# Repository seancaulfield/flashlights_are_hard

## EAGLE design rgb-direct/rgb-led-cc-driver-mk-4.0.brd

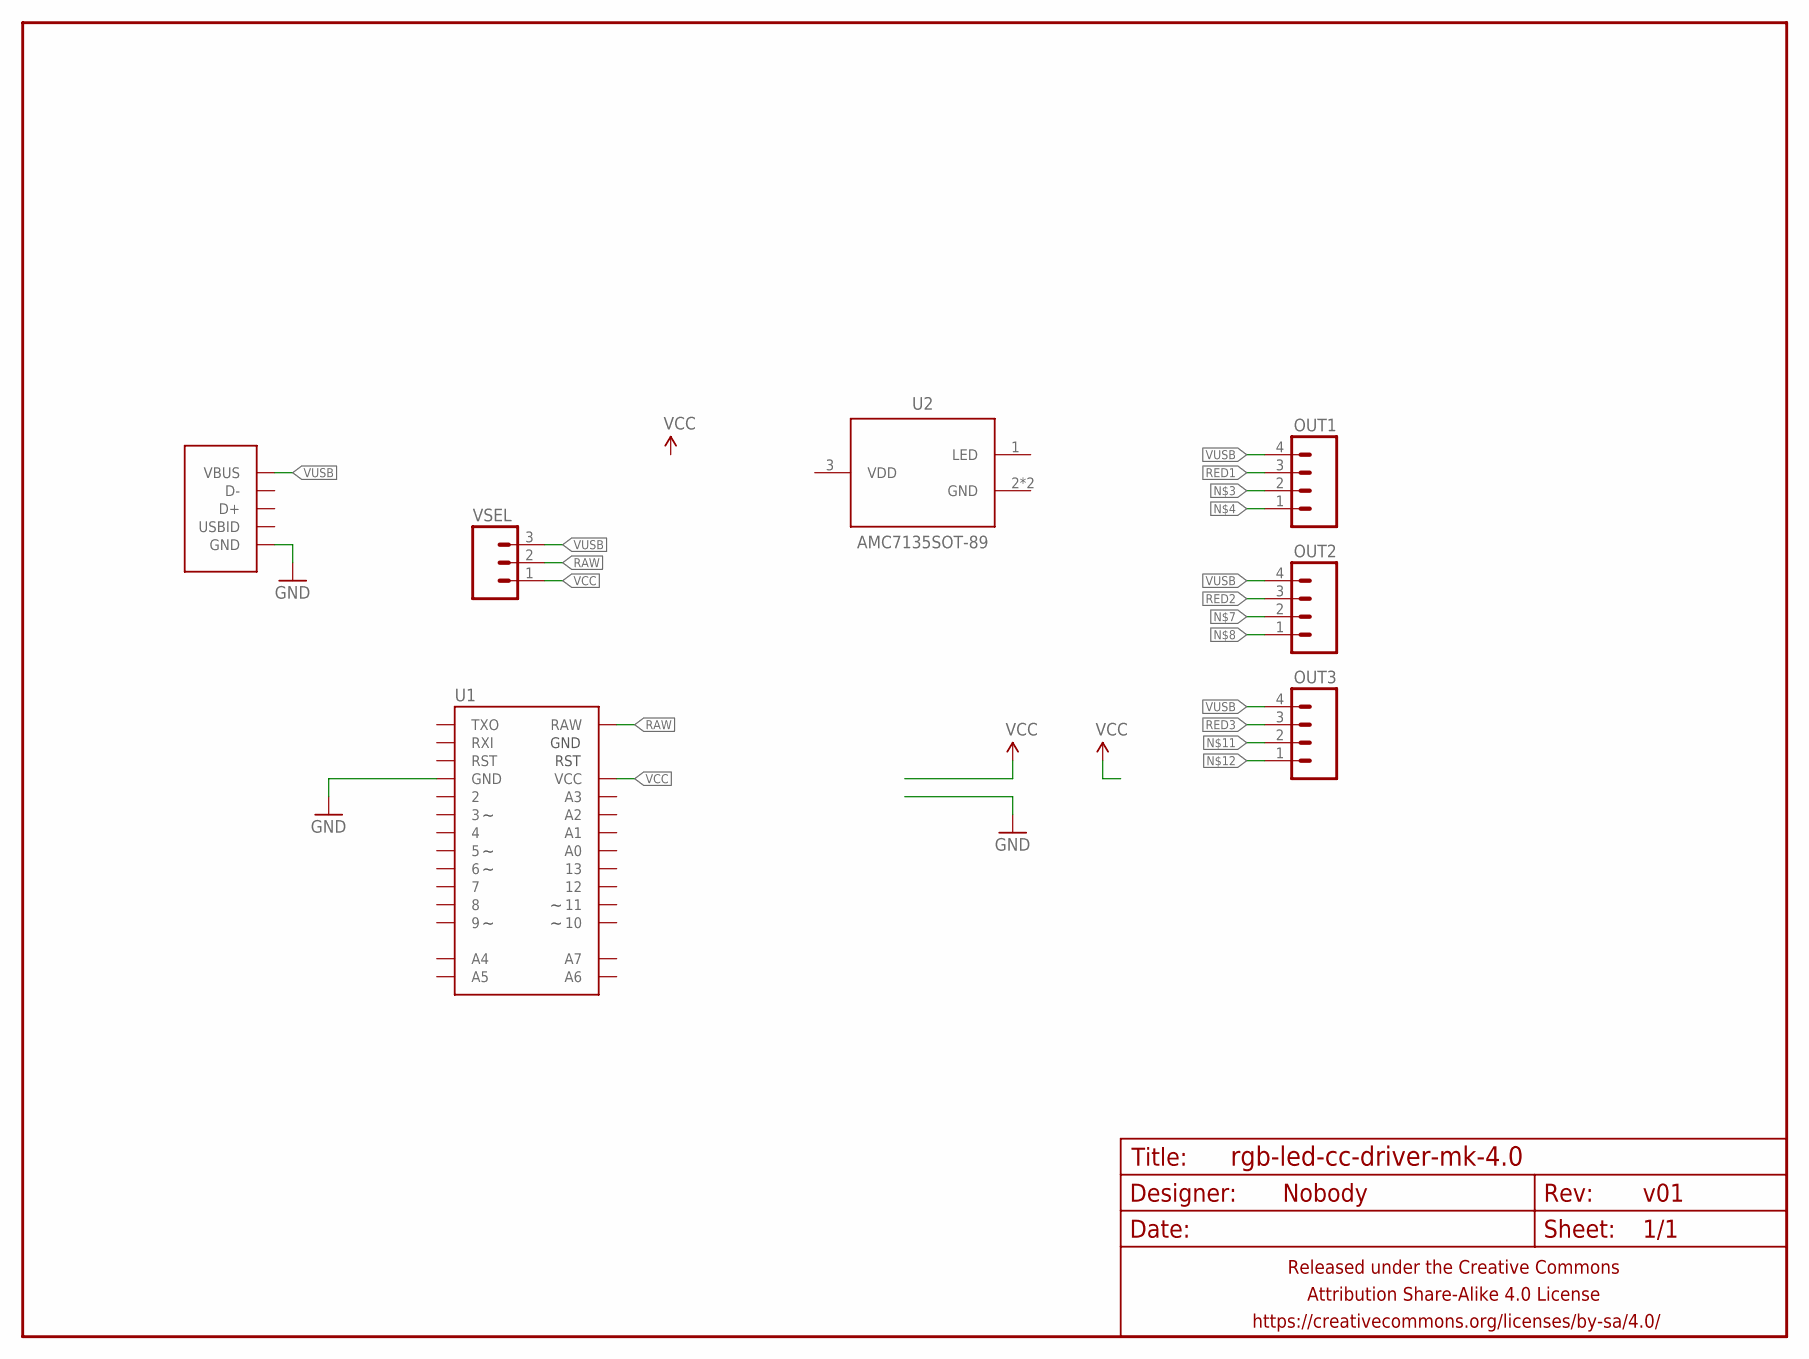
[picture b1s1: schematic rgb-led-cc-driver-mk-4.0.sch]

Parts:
FRAME1: FRAME-LETTERNO_PACKAGE; DUMMY
OUT1, OUT2, OUT3: M04JST-PTH; JST-4-PH-RA-PTH
PWR: USB-ABCOMBO-PWR; USB-MICRO-B-FCI-CUTOUT2
U1: ARDUINO-PRO-MINI-NO-FTDIARDUINO-PRO-MINI-NO-FTDI; ARDUINO_PRO_MINI_NO_FTDI
U2: AMC7135SOT-89; SOT89
VSEL: M03PTH; 1X03

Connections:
GND: PWR.5 (GND), PWR.P$1 (GND), PWR.P$2 (GND), U1.GND@1 (GND), U1.GND@2 (GND)
RAW: U1.RAW, VSEL.2
RED1: OUT1.3
RED2: OUT2.3
RED3: OUT3.3
VCC: U1.VCC, VSEL.1
VUSB: OUT1.4, OUT2.4, OUT3.4, PWR.1 (VBUS), VSEL.3

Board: 2 copper layers, 11 parts (2 on the bottom side), 4 nets, no tracks yet.

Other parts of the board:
U$1: CC-BY-SA-4.0-NO-URL
U$2: COW_SMALL
U$3: OSHWLOGO_BOT_0.2_A

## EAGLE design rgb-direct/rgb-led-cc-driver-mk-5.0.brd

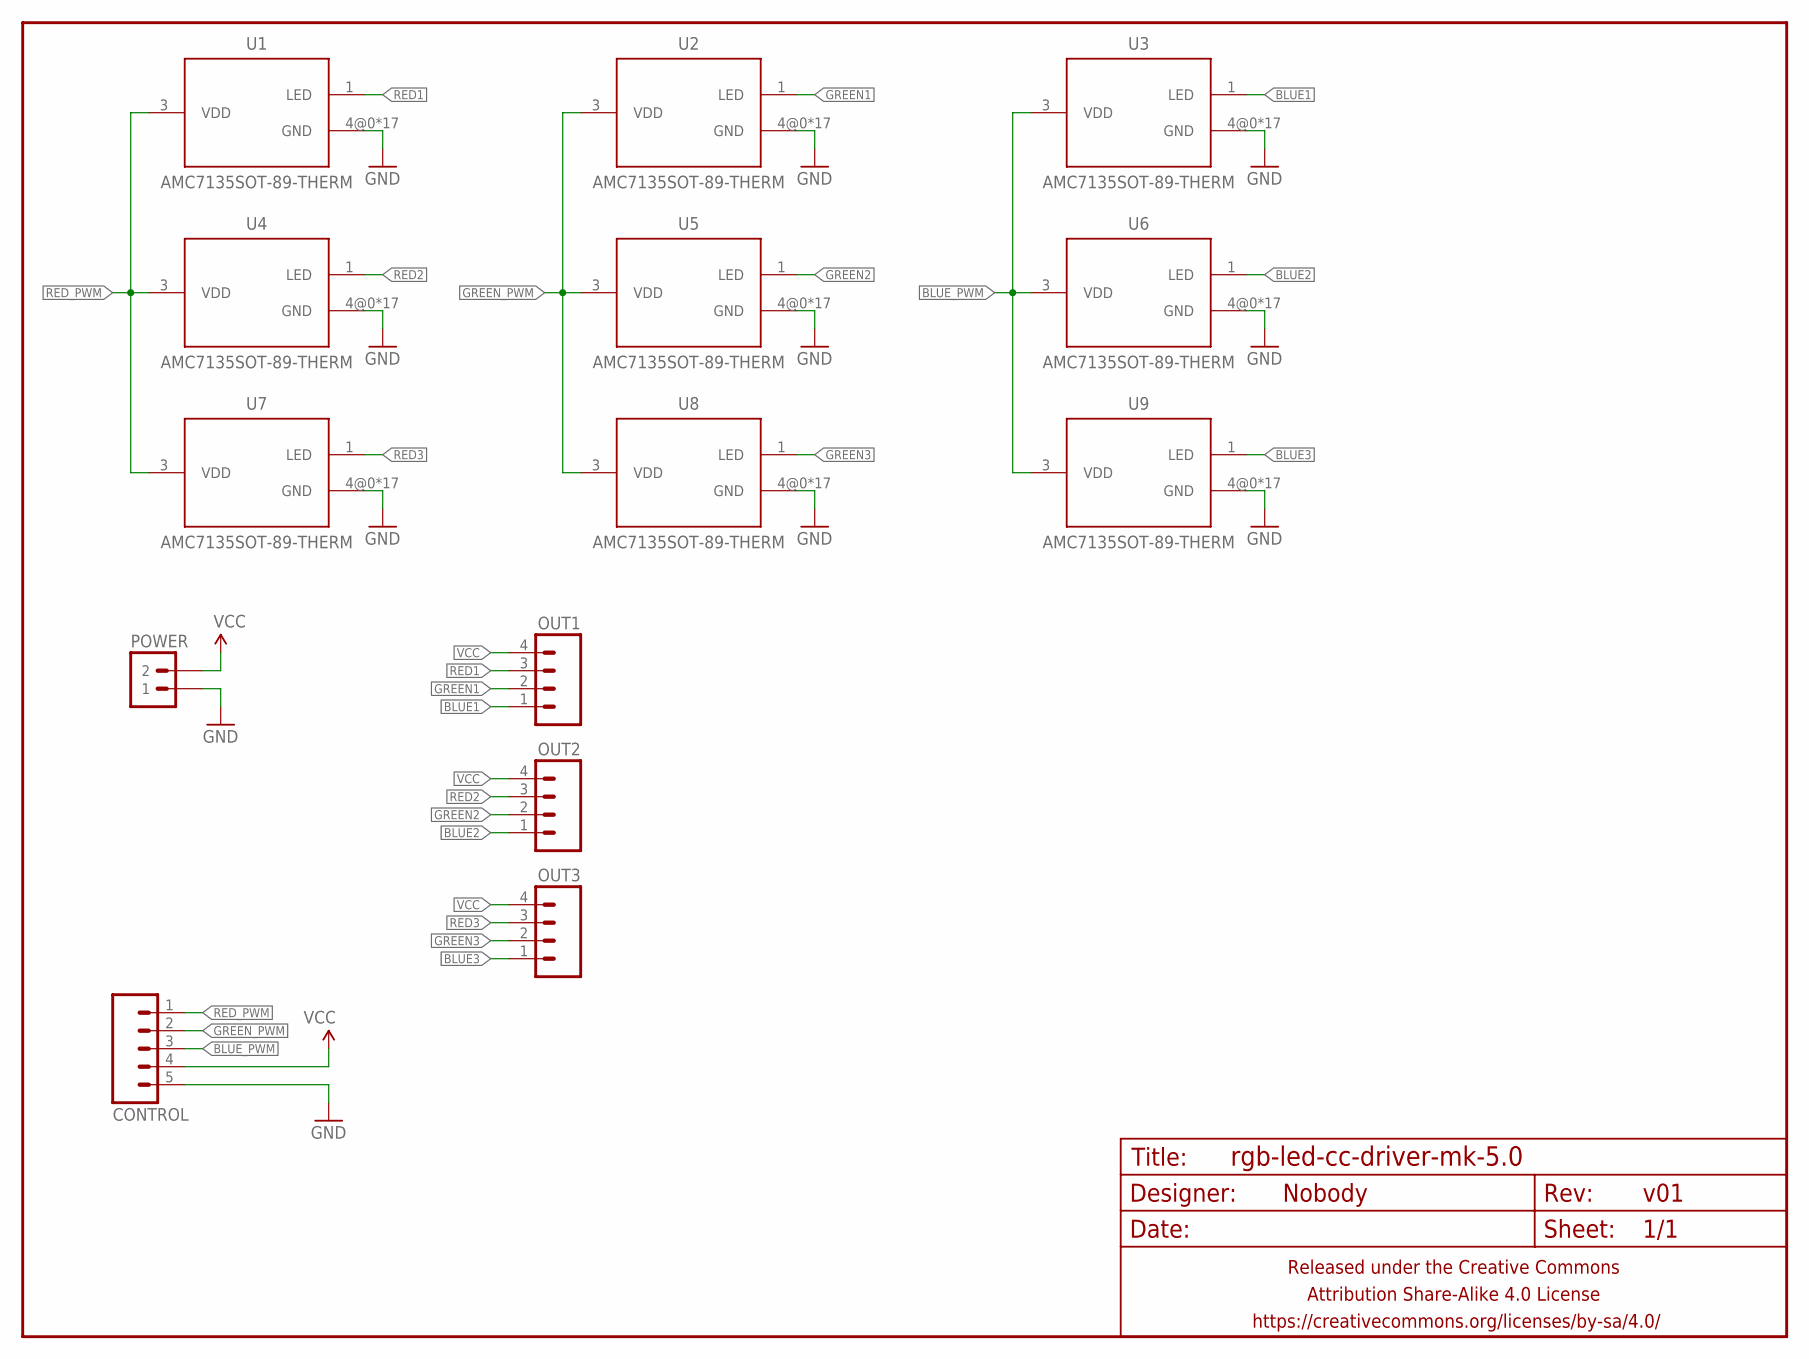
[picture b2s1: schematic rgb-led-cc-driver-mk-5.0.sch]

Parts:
CONTROL: M05JST-PH-RA-PTH; JST-5-PH-RA-PTH
FRAME1: FRAME-LETTERNO_PACKAGE; DUMMY
OUT1, OUT2, OUT3: M04JST-PTH; JST-4-PH-RA-PTH
POWER: M02PTH4; 1X02_XTRA_BIG
U1, U2, U3, U4, U5, U6, U7, U8, U9: AMC7135SOT-89-THERM; SOT89-THERM

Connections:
BLUE1: OUT1.1, U3.1 (LED)
BLUE2: OUT2.1, U6.1 (LED)
BLUE3: OUT3.1, U9.1 (LED)
BLUE_PWM: CONTROL.3, U3.3 (VDD), U6.3 (VDD), U9.3 (VDD)
GND: CONTROL.5, POWER.1, U1.4@0 (GND), U1.4@1 (GND), U1.4@2 (GND), U1.4@3 (GND), U1.4@4 (GND), U1.4@5 (GND), U1.4@6 (GND), U1.4@7 (GND), U1.4@8 (GND), U1.4@9 (GND), U1.4@10 (GND), U1.4@11 (GND), U1.4@12 (GND), U1.4@13 (GND), U1.4@14 (GND), U1.4@15 (GND), U1.4@16 (GND), U2.4@0 (GND), U2.4@1 (GND), U2.4@2 (GND), U2.4@3 (GND), U2.4@4 (GND), U2.4@5 (GND), U2.4@6 (GND), U2.4@7 (GND), U2.4@8 (GND), U2.4@9 (GND), U2.4@10 (GND), U2.4@11 (GND), U2.4@12 (GND), U2.4@13 (GND), U2.4@14 (GND), U2.4@15 (GND), U2.4@16 (GND), U3.4@0 (GND), U3.4@1 (GND), U3.4@2 (GND), U3.4@3 (GND), U3.4@4 (GND), U3.4@5 (GND), U3.4@6 (GND), U3.4@7 (GND), U3.4@8 (GND), U3.4@9 (GND), U3.4@10 (GND), U3.4@11 (GND), U3.4@12 (GND), U3.4@13 (GND), U3.4@14 (GND), U3.4@15 (GND), U3.4@16 (GND), U4.4@0 (GND), U4.4@1 (GND), U4.4@2 (GND), U4.4@3 (GND), U4.4@4 (GND), U4.4@5 (GND), U4.4@6 (GND), U4.4@7 (GND), U4.4@8 (GND), U4.4@9 (GND), U4.4@10 (GND), U4.4@11 (GND), U4.4@12 (GND), U4.4@13 (GND), U4.4@14 (GND), U4.4@15 (GND), U4.4@16 (GND), U5.4@0 (GND), U5.4@1 (GND), U5.4@2 (GND), U5.4@3 (GND), U5.4@4 (GND), U5.4@5 (GND), U5.4@6 (GND), U5.4@7 (GND), U5.4@8 (GND), U5.4@9 (GND), U5.4@10 (GND), U5.4@11 (GND), U5.4@12 (GND), U5.4@13 (GND), U5.4@14 (GND), U5.4@15 (GND), U5.4@16 (GND), U6.4@0 (GND), U6.4@1 (GND), U6.4@2 (GND), U6.4@3 (GND), U6.4@4 (GND), U6.4@5 (GND), U6.4@6 (GND), U6.4@7 (GND), U6.4@8 (GND), U6.4@9 (GND), U6.4@10 (GND), U6.4@11 (GND), U6.4@12 (GND), U6.4@13 (GND), U6.4@14 (GND), U6.4@15 (GND), U6.4@16 (GND), U7.4@0 (GND), U7.4@1 (GND), U7.4@2 (GND), U7.4@3 (GND), U7.4@4 (GND), U7.4@5 (GND), U7.4@6 (GND), U7.4@7 (GND), U7.4@8 (GND), U7.4@9 (GND), U7.4@10 (GND), U7.4@11 (GND), U7.4@12 (GND), U7.4@13 (GND), U7.4@14 (GND), U7.4@15 (GND), U7.4@16 (GND), U8.4@0 (GND), U8.4@1 (GND), U8.4@2 (GND), U8.4@3 (GND), U8.4@4 (GND), U8.4@5 (GND), U8.4@6 (GND), U8.4@7 (GND), U8.4@8 (GND), U8.4@9 (GND), U8.4@10 (GND), U8.4@11 (GND), U8.4@12 (GND), U8.4@13 (GND), U8.4@14 (GND), U8.4@15 (GND), U8.4@16 (GND), U9.4@0 (GND), U9.4@1 (GND), U9.4@2 (GND), U9.4@3 (GND), U9.4@4 (GND), U9.4@5 (GND), U9.4@6 (GND), U9.4@7 (GND), U9.4@8 (GND), U9.4@9 (GND), U9.4@10 (GND), U9.4@11 (GND), U9.4@12 (GND), U9.4@13 (GND), U9.4@14 (GND), U9.4@15 (GND), U9.4@16 (GND)
GREEN1: OUT1.2, U2.1 (LED)
GREEN2: OUT2.2, U5.1 (LED)
GREEN3: OUT3.2, U8.1 (LED)
GREEN_PWM: CONTROL.2, U2.3 (VDD), U5.3 (VDD), U8.3 (VDD)
RED1: OUT1.3, U1.1 (LED)
RED2: OUT2.3, U4.1 (LED)
RED3: OUT3.3, U7.1 (LED)
RED_PWM: CONTROL.1, U1.3 (VDD), U4.3 (VDD), U7.3 (VDD)
VCC: CONTROL.4, OUT1.4, OUT2.4, OUT3.4, POWER.2

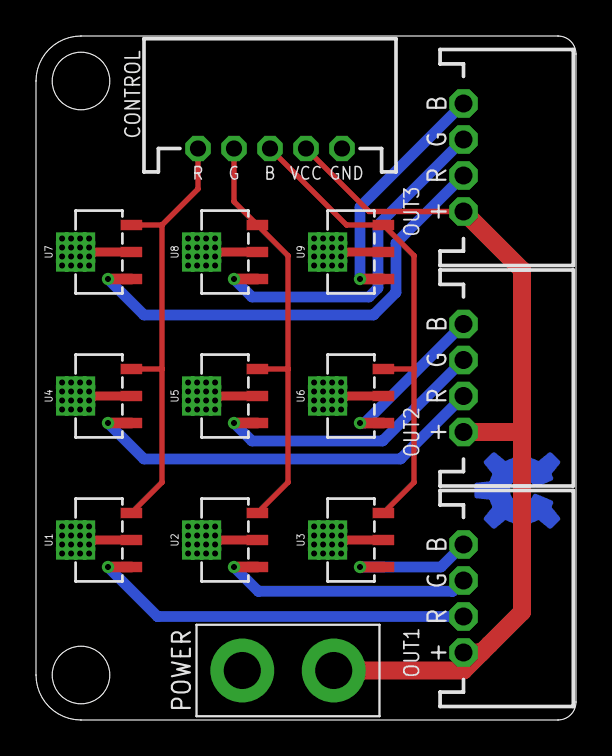
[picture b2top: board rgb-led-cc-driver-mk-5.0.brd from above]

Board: 2 copper layers, 30.0 x 38.0 mm, 17 parts (1 on the bottom side), 14 nets.

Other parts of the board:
U$1: CC-BY-SA-4.0-NO-URL
U$3: OSHWLOGO_BOT_0.2_A

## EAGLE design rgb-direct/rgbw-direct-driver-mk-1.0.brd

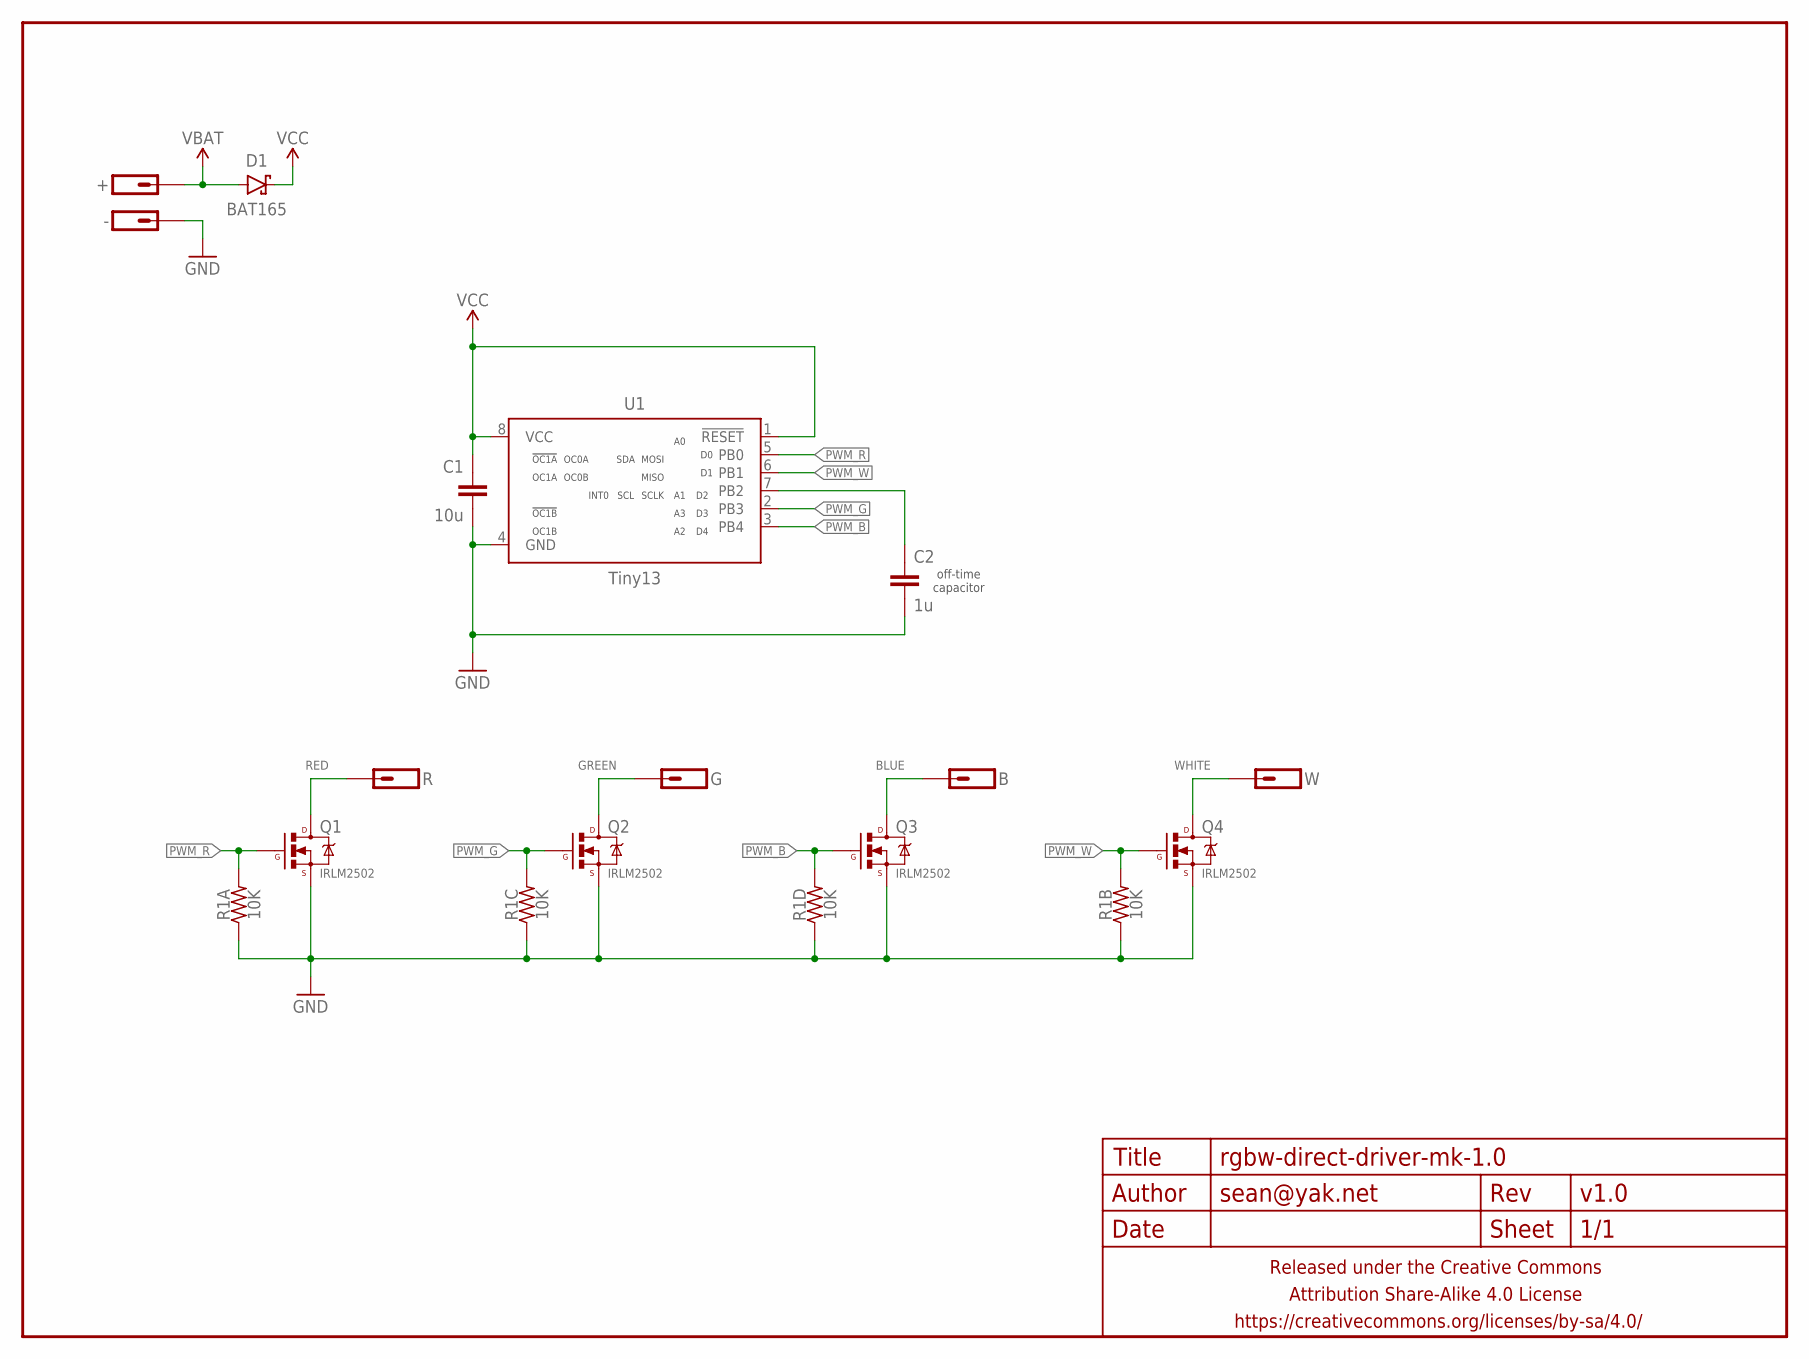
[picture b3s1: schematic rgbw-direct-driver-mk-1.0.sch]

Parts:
+: M01PTH-1MM-CIR-NS; 1X01-1MM-CIR-NS
-: M01NOT-A-VIA-NOPE; 1X01_NOSILK_NOSTOP
B: M01SMD-1.25MM-DIA; 1X01-SMD-1.25MM-DIA-NS
C1: 10u; C0603-TIGHTER
C2: 1u; C0402
D1: BAT165; SOD323-SCHOTTKY
FRAME1: FRAME-LETTERNO_PACKAGE; DUMMY
G: M01SMD-1.25MM-DIA; 1X01-SMD-1.25MM-DIA-NS
Q1, Q2, Q3, Q4: IRLM2502; SOT23-CLOSER
R: M01SMD-1.25MM-DIA; 1X01-SMD-1.25MM-DIA-NS
R1: 10K; R1206-ARRAY-4
U1: Tiny13; SO08-NARROWER
W: M01SMD-1.25MM-DIA; 1X01-SMD-1.25MM-DIA-NS

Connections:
BLUE: B.P$1, Q3.3 (D)
GND: -.P$1, C1.2, C2.2, Q1.2 (S), Q2.2 (S), Q3.2 (S), Q4.2 (S), R1.A1 (1), R1.B1 (1), R1.C1 (1), R1.D1 (1), U1.4 (GND)
GREEN: G.P$1, Q2.3 (D)
unnamed: C2.1, U1.7 (PB2)
PWM_B: Q3.1 (G), R1.D2 (2), U1.3 (PB4)
PWM_G: Q2.1 (G), R1.C2 (2), U1.2 (PB3)
PWM_R: Q1.1 (G), R1.A2 (2), U1.5 (PB0)
PWM_W: Q4.1 (G), R1.B2 (2), U1.6 (PB1)
RED: Q1.3 (D), R.P$1
VBAT: +.1, D1.A
VCC: C1.1, D1.C, U1.1 (!RESET), U1.8 (VCC)
WHITE: Q4.3 (D), W.P$1

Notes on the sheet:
off-time capacitor

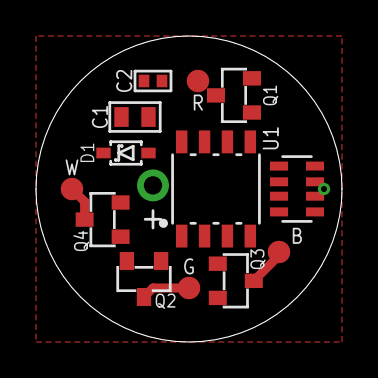
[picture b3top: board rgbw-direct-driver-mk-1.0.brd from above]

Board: 2 copper layers, 17.0 x 17.0 mm, 16 parts (1 on the bottom side), 12 nets.

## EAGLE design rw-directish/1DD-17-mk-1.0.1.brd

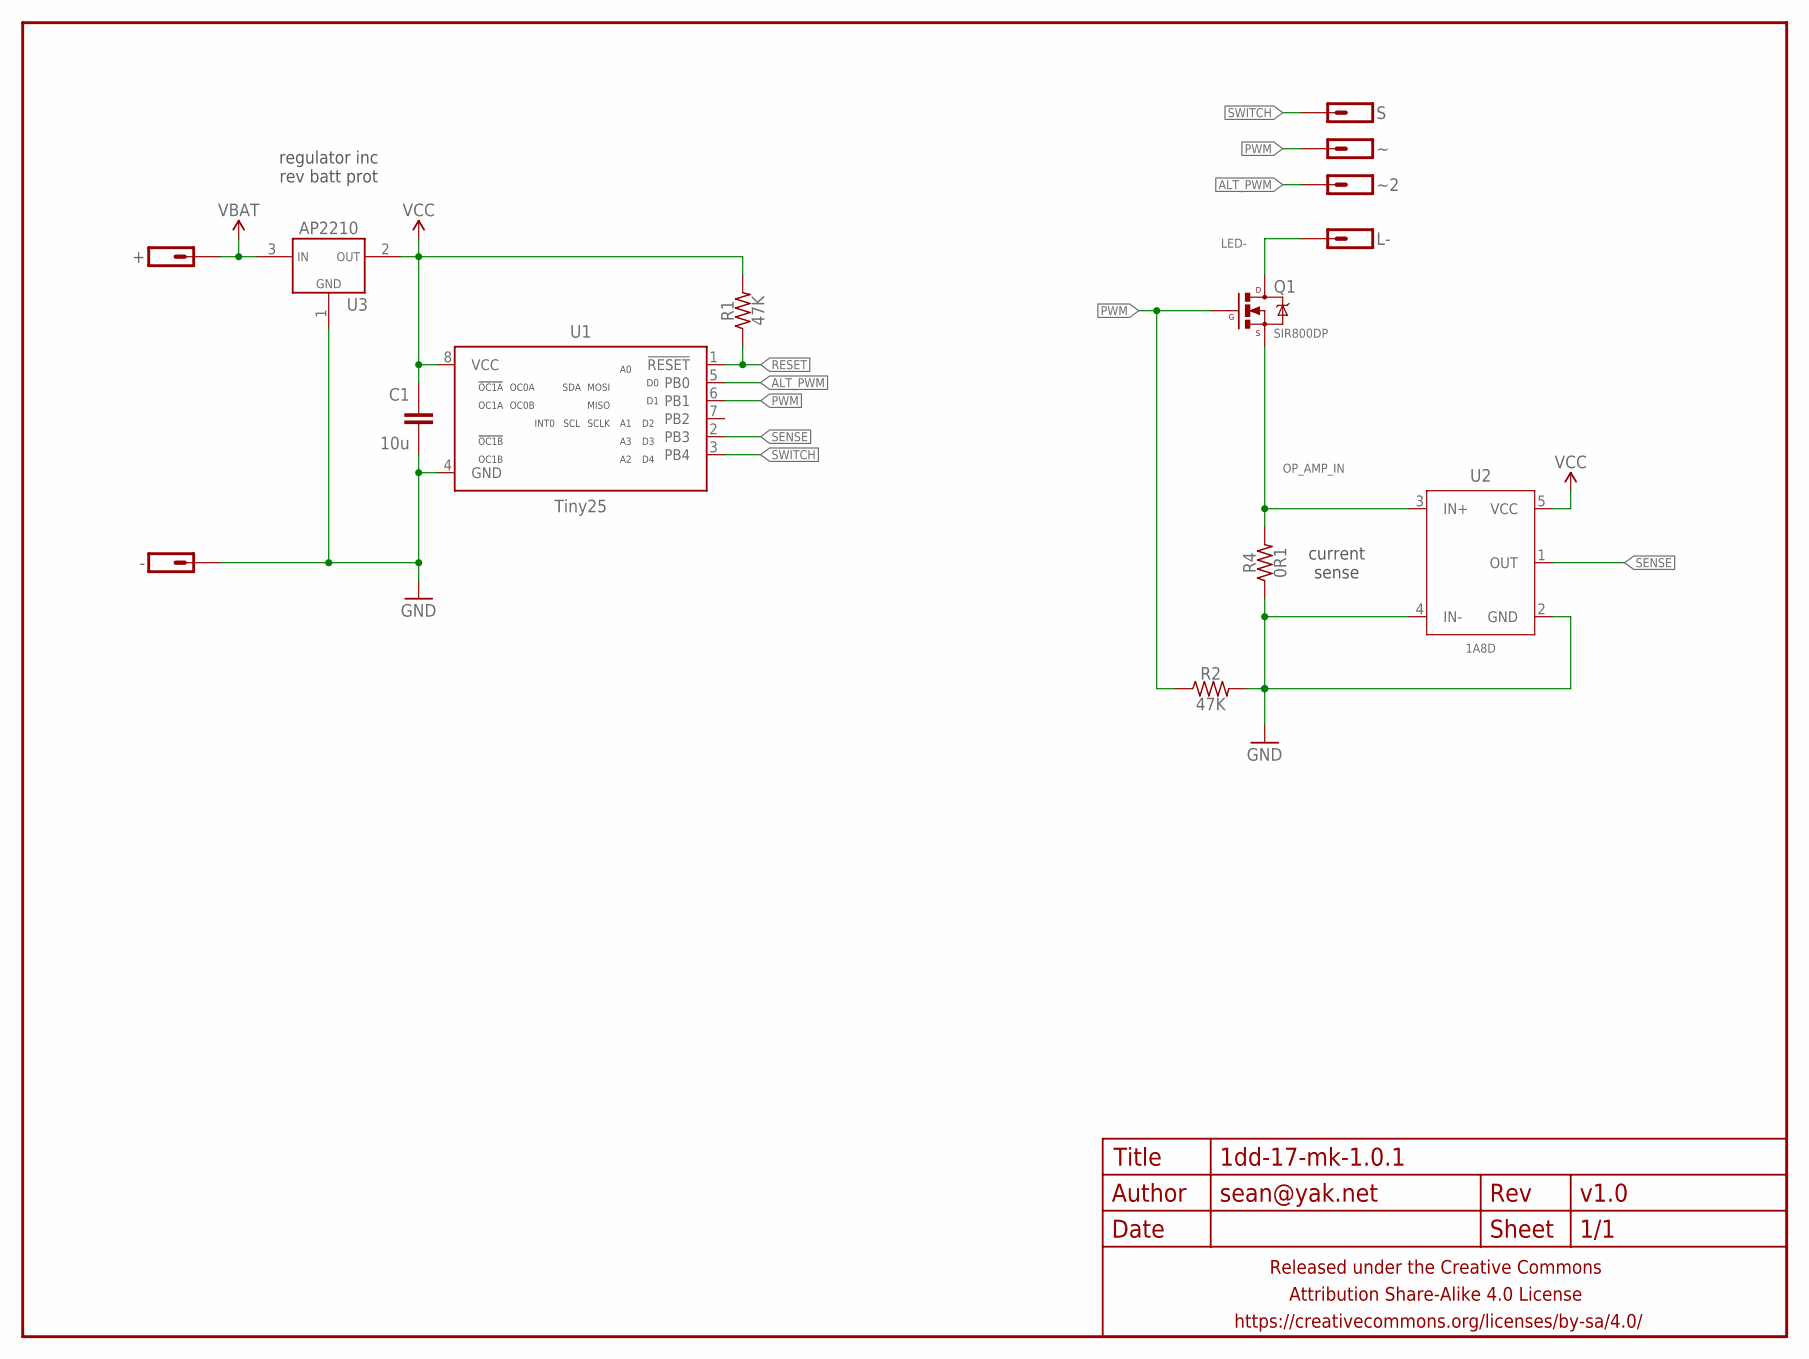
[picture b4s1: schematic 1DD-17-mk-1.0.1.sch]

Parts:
+: M01PTH-1MM-CIR-NS; 1X01-1MM-CIR-NS
-: M01NOT-A-VIA-NOPE; 1X01_NOSILK_NOSTOP
C1: 10u; C0603-TIGHTER
FRAME1: FRAME-LETTERNO_PACKAGE; DUMMY
L-: M01SMD-1.5MM-DIA-NS; 1X01-SMD-1.5MM-DIA-NS
Q1: SIR800DP; POWERPACK-SO-8
R1, R2: 47K; R0402
R4: 0R1; R1206
S: M01SMD-1MM-DIA-NS; 1X01-SMD-1MM-DIA-NS
U1: Tiny25; SO08-NARROWER
U2: 1A8D; SOT23-5-SLIM
U3: AP2210; SOT23-3
~, ~2: M01SMD-1MM-DIA-NS; 1X01-SMD-1MM-DIA-NS

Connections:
ALT_PWM: U1.5 (PB0), ~2.P$1
GND: -.P$1, C1.2, R2.2, R4.1, U1.4 (GND), U2.2 (GND), U2.4 (IN-), U3.1 (GND)
LED-: L-.P$1, Q1.5678 (D)
OP_AMP_IN: Q1.1 (S), Q1.2 (S), Q1.3 (S), R4.2, U2.3 (IN+)
PWM: Q1.4 (G), R2.1, U1.6 (PB1), ~.P$1
RESET: R1.1, U1.1 (!RESET)
SENSE: U1.2 (PB3), U2.1 (OUT)
SWITCH: S.P$1, U1.3 (PB4)
VBAT: +.1, U3.3 (VIN)
VCC: C1.1, R1.2, U1.8 (VCC), U2.5 (VCC), U3.2 (VOUT)

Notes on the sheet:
current sense
regulator inc rev batt prot

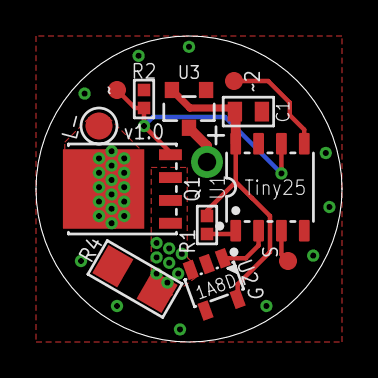
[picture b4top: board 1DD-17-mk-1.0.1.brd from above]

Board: 2 copper layers, 17.0 x 17.0 mm, 15 parts (1 on the bottom side), 10 nets.

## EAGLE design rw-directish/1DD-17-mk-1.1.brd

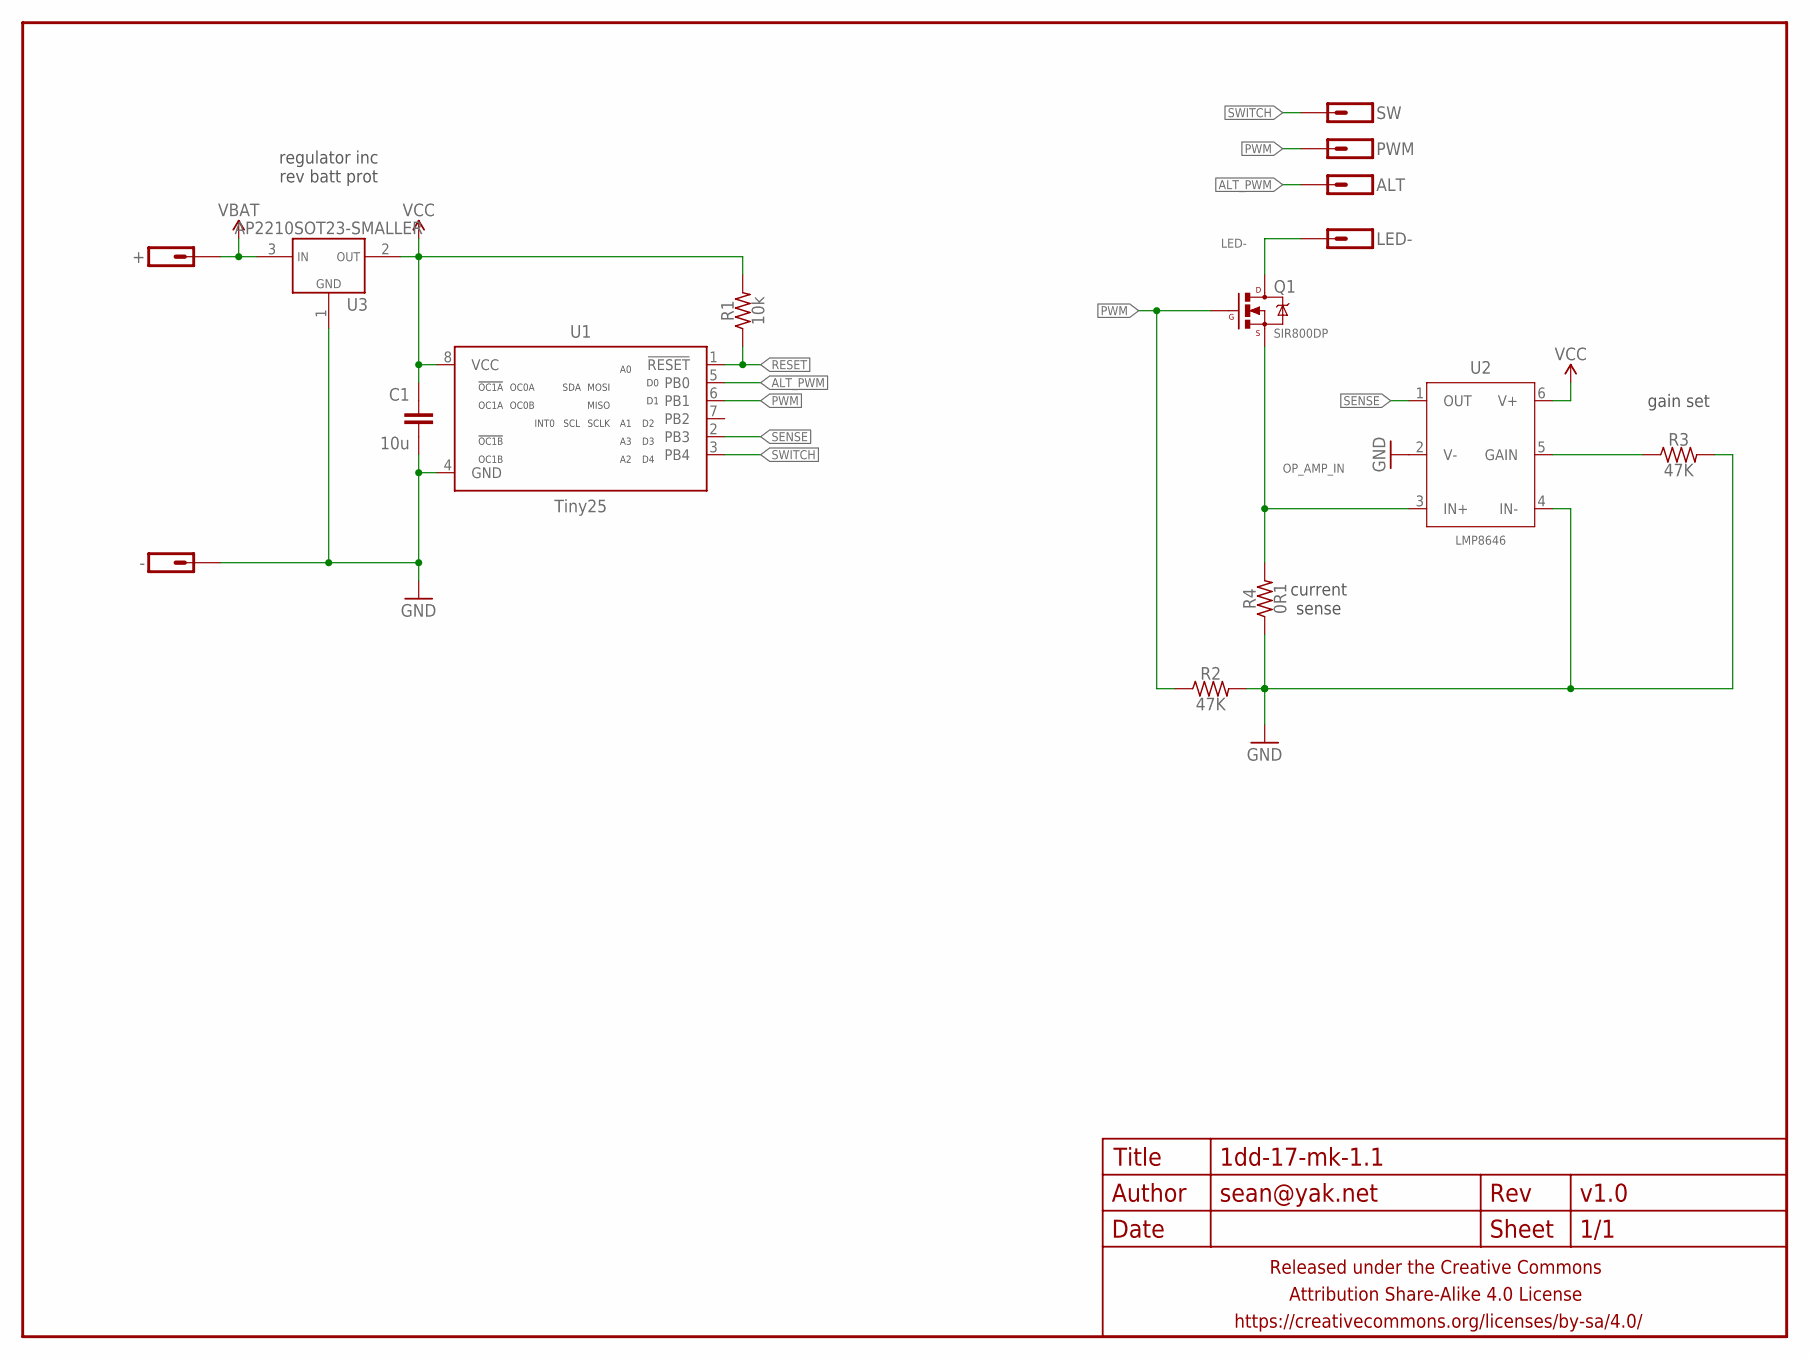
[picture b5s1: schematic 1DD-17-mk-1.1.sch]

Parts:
+: M01PTH-1MM-CIR-NS; 1X01-1MM-CIR-NS
-: M01NOT-A-VIA-NOPE; 1X01_NOSILK_NOSTOP
ALT: M01SMD-1MM-DIA-NS; 1X01-SMD-1MM-DIA-NS
C1: 10u; C0603-TIGHTER
FRAME1: FRAME-LETTERNO_PACKAGE; DUMMY
LED-: M011X01-0.9MM-CIR; 1X01-0.9MM-CIR
PWM: M01SMD-1MM-DIA-NS; 1X01-SMD-1MM-DIA-NS
Q1: SIR800DP; POWERPACK-SO-8
R1: 10k; R0402
R2, R3: 47K; R0402
R4: 0R1; R1206
SW: M01SMD-1MM-DIA-NS; 1X01-SMD-1MM-DIA-NS
U1: Tiny25; SO08-NARROWER
U2: LMP8646; SOT23-6
U3: AP2210SOT23-SMALLER; SOT23-3

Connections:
ALT_PWM: ALT.P$1, U1.5 (PB0)
GND: -.P$1, C1.2, R2.2, R3.2, R4.1, U1.4 (GND), U2.2 (V-), U2.4 (IN-), U3.1 (GND)
LED-: LED-.P$1, Q1.5678 (D)
unnamed: R3.1, U2.5 (GAIN)
OP_AMP_IN: Q1.1 (S), Q1.2 (S), Q1.3 (S), R4.2, U2.3 (IN+)
PWM: PWM.P$1, Q1.4 (G), R2.1, U1.6 (PB1)
RESET: R1.1, U1.1 (!RESET)
SENSE: U1.2 (PB3), U2.1 (OUT)
SWITCH: SW.P$1, U1.3 (PB4)
VBAT: +.1, U3.3 (VIN)
VCC: C1.1, R1.2, U1.8 (VCC), U2.6 (V+), U3.2 (VOUT)

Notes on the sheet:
current sense
gain set
regulator inc rev batt prot

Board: 2 copper layers, 16 parts (1 on the bottom side), 11 nets, no tracks yet.

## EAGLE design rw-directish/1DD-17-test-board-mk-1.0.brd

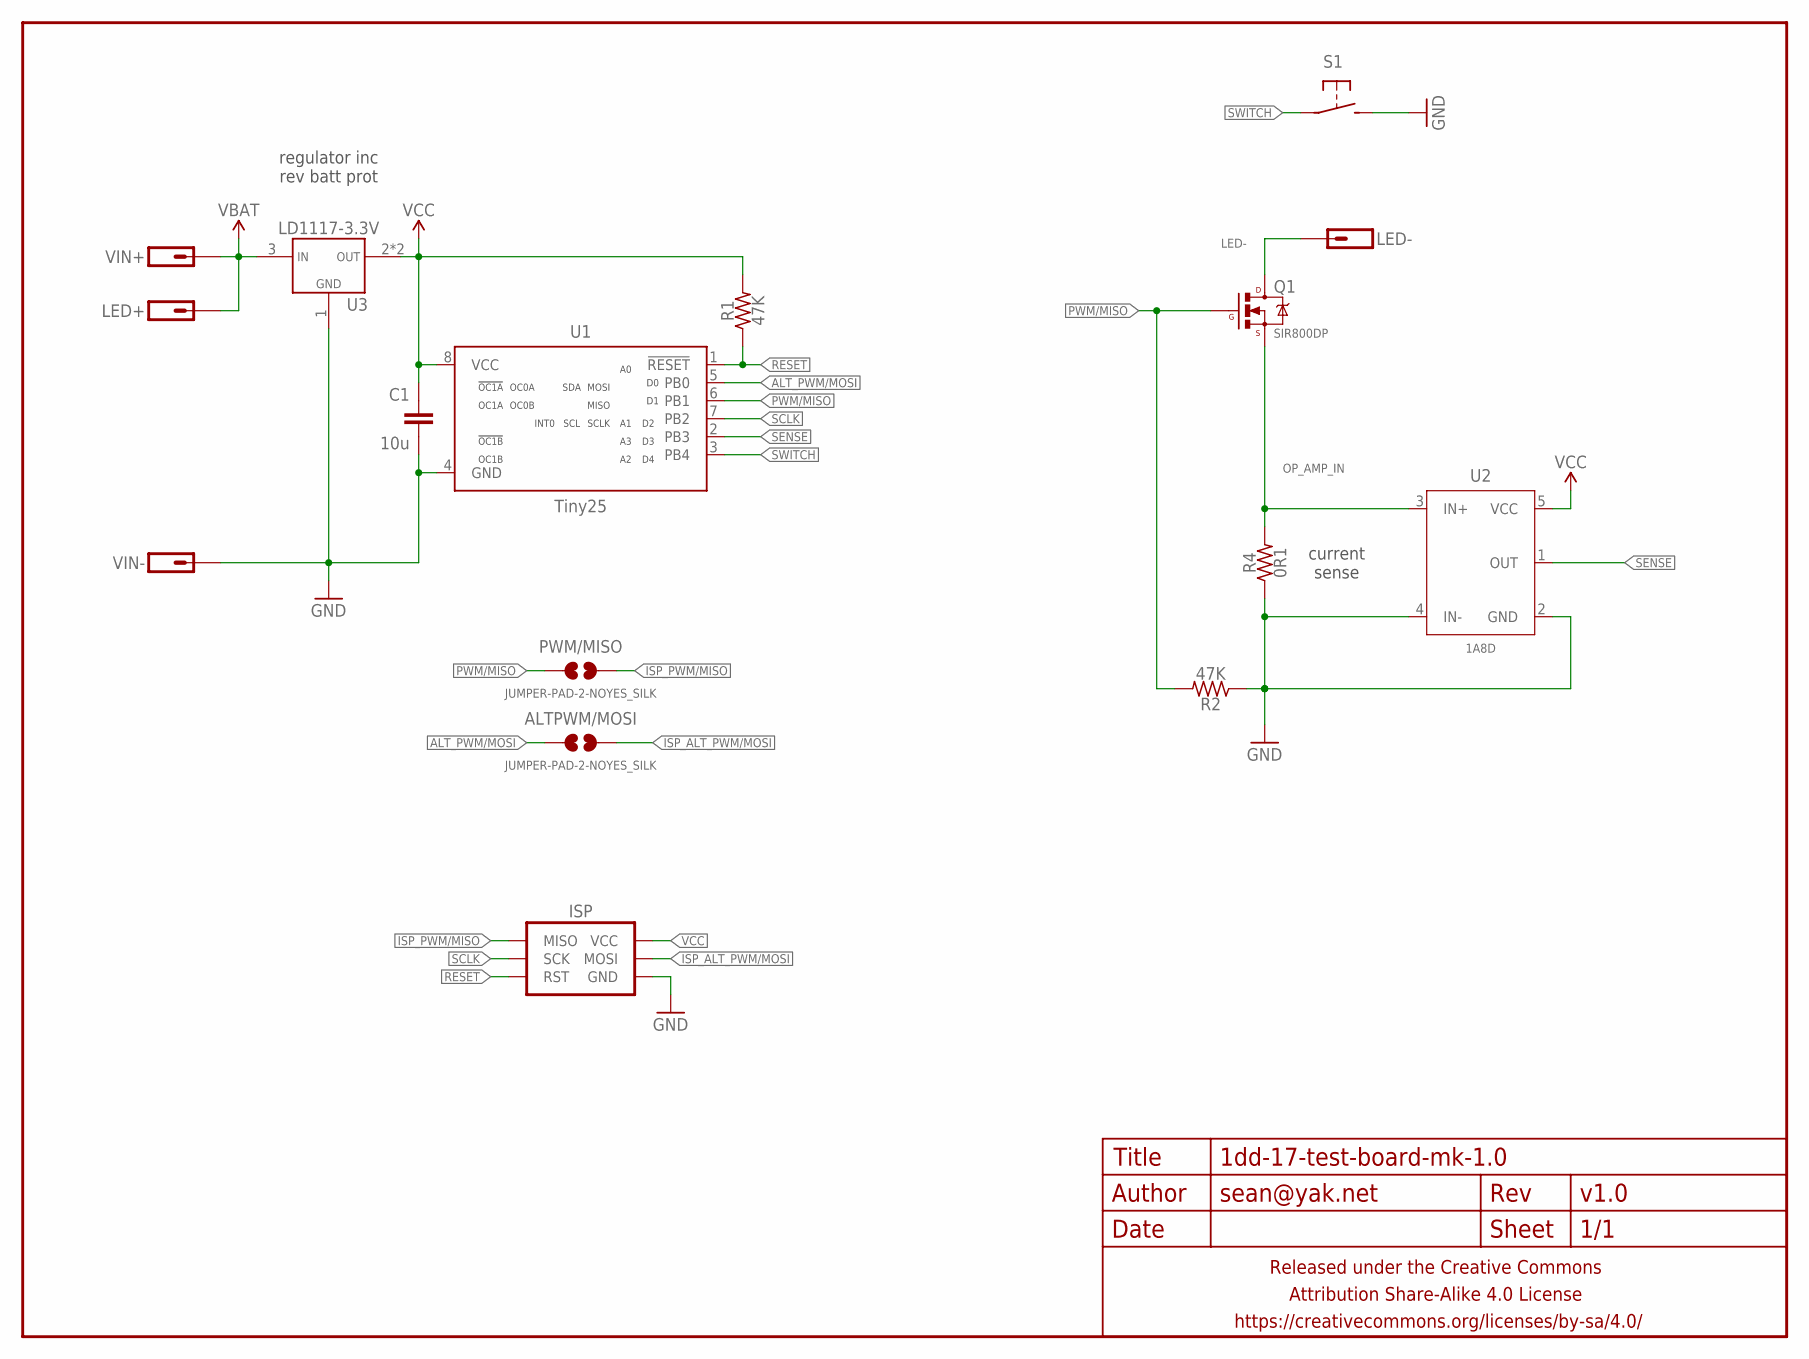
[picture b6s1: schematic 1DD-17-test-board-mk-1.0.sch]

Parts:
ALTPWM/MOSI: JUMPER-PAD-2-NOYES_SILK; PAD-JUMPER-2-NO_YES_SILK
C1: 10u; C0805-TIGHTER
FRAME1: FRAME-LETTERNO_PACKAGE; DUMMY
ISP: AVR_SPI_PRG_6PTH; 2X3
LED+: M01OFFSET; 1X01_OFFSET
LED-: M01OFFSET; 1X01_OFFSET
PWM/MISO: JUMPER-PAD-2-NOYES_SILK; PAD-JUMPER-2-NO_YES_SILK
Q1: SIR800DP; POWERPACK-SO-8
R1, R2: 47K; R0603-TIGHTER
R4: 0R1; R1206
S1: SPST-NO-TACT3MM-PTH-SMALL-PADS; DTS-3-SMALL-PADS
U1: Tiny25; SO08-NARROWER
U2: 1A8D; SOT23-5-SLIM
U3: LD1117-3.3V; SOT223
VIN+: M01OFFSET; 1X01_OFFSET
VIN-: M01OFFSET; 1X01_OFFSET

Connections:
ALT_PWM/MOSI: ALTPWM/MOSI.1, U1.5 (PB0)
GND: C1.2, ISP.6 (GND), R2.1, R4.1, S1.2, U1.4 (GND), U2.2 (GND), U2.4 (IN-), U3.1 (GND), VIN-.1
ISP_ALT_PWM/MOSI: ALTPWM/MOSI.2, ISP.4 (MOSI)
ISP_PWM/MISO: ISP.1 (MISO), PWM/MISO.2
LED-: LED-.1, Q1.5678 (D)
OP_AMP_IN: Q1.1 (S), Q1.2 (S), Q1.3 (S), R4.2, U2.3 (IN+)
PWM/MISO: PWM/MISO.1, Q1.4 (G), R2.2, U1.6 (PB1)
RESET: ISP.5 (RST), R1.1, U1.1 (!RESET)
SCLK: ISP.3 (SCK), U1.7 (PB2)
SENSE: U1.2 (PB3), U2.1 (OUT)
SWITCH: S1.1, U1.3 (PB4)
VBAT: LED+.1, U3.3 (VIN), VIN+.1
VCC: C1.1, ISP.2 (VCC), R1.2, U1.8 (VCC), U2.5 (VCC), U3.2 (VOUT), U3.4 (VOUT)

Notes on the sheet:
current sense
regulator inc rev batt prot

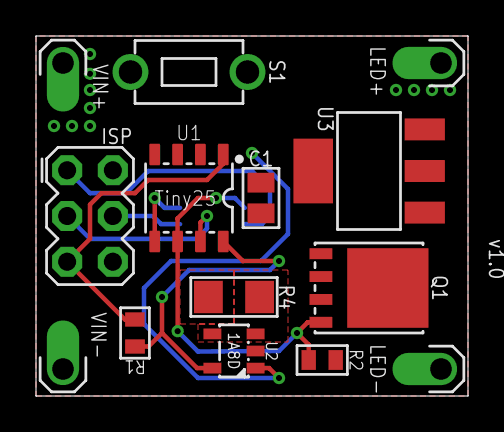
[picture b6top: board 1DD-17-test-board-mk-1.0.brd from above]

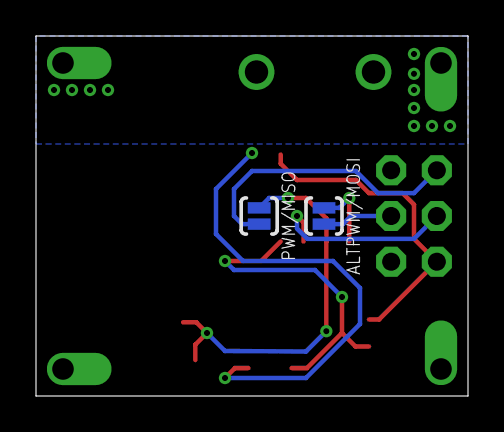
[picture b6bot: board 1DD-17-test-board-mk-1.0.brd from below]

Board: 2 copper layers, 24.0 x 20.0 mm, 17 parts (2 on the bottom side), 13 nets.

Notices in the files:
parts and their libraries:
A_butts: Released under the Creative Commons Attribution Share-Alike 4.0 License
A_butts: https://creativecommons.org/licenses/by-sa/4.0
A_butts: Released under the Creative Commons
